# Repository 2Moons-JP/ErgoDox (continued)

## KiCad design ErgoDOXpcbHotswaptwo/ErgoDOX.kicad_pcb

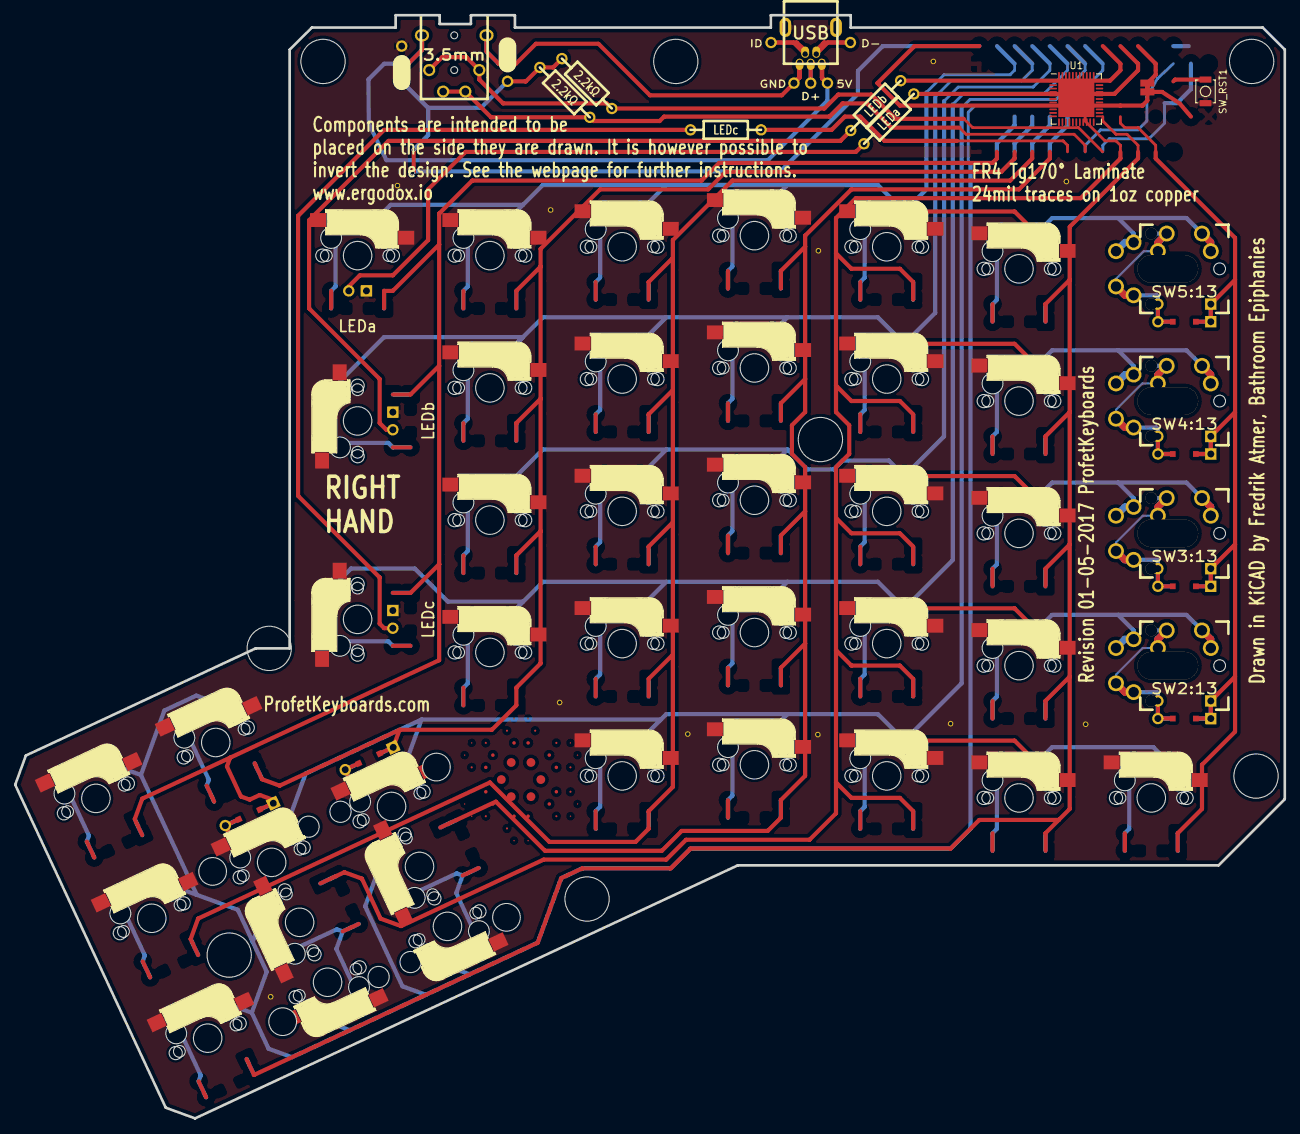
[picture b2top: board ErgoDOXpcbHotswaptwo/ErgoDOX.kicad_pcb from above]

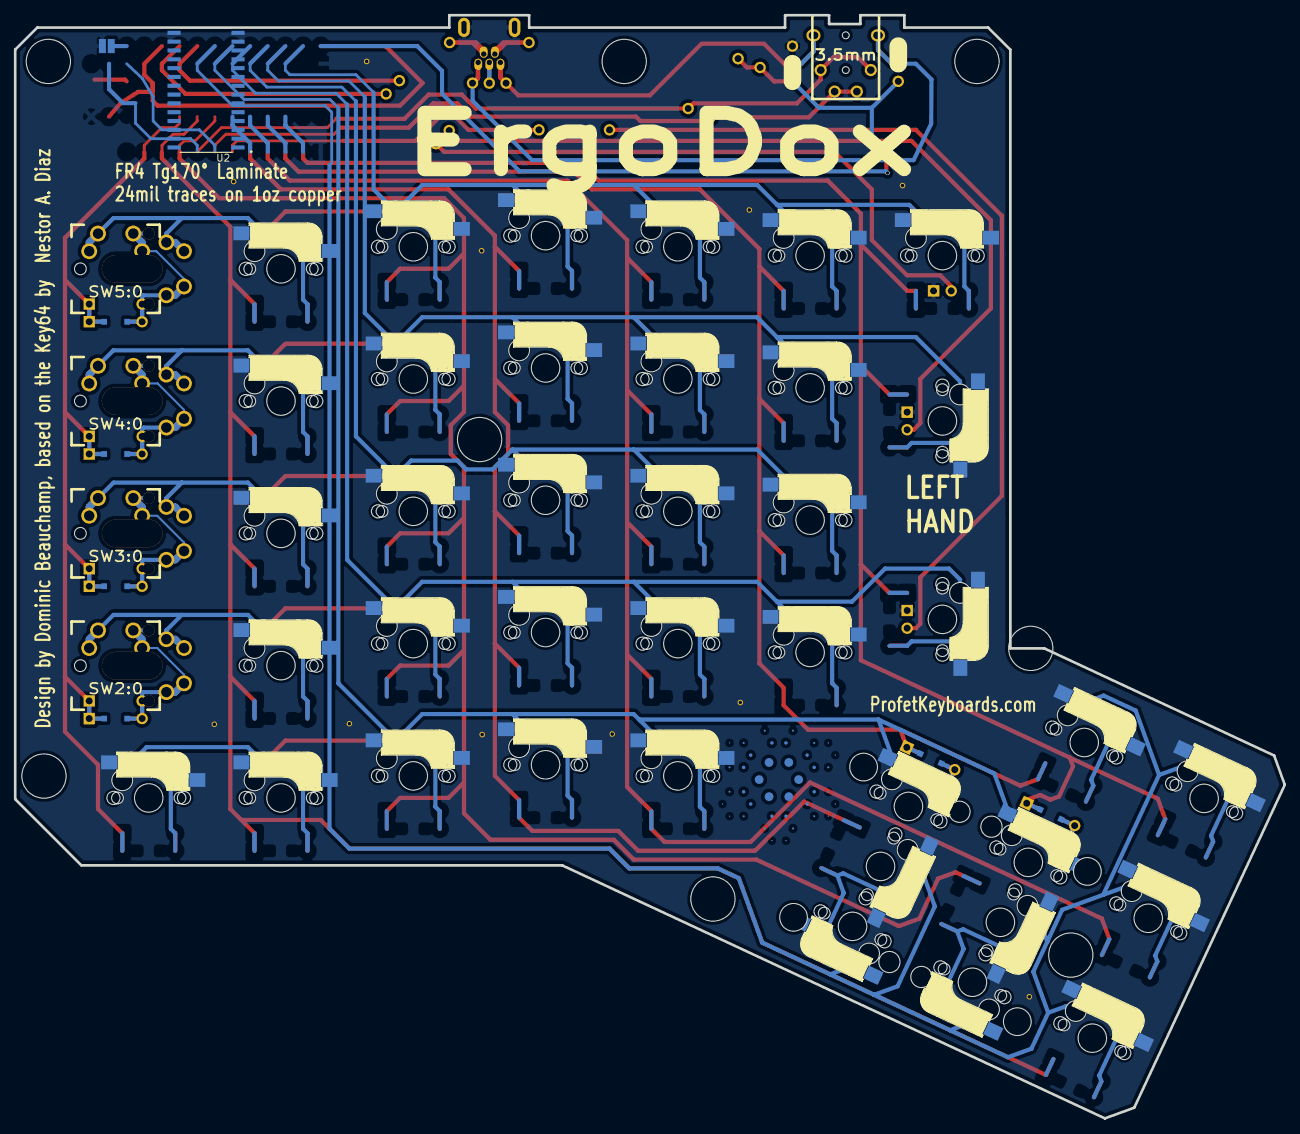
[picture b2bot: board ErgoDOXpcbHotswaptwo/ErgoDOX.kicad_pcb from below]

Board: 2 copper layers, 182.8 x 158.9 mm, 77 parts (4 on the bottom side), 36 nets.

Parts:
D1:7, D1:8: D; DIODE
H99: MECHANICAL; ErgoDOXmech
J1: USB; USBMINImod
J2: 3.5mm; 4pin35mmAudio
J3, J4: JMP; 100PITCH1X3
JP1, JP2: JUMPER; GAP
LED_A1: LEDa; MX_LED
LED_B1: LEDb; MX_LED
LED_C1: LEDc; MX_LED
R1, R2: 2.2kΩ; RESISTOR
RA1: LEDa; RESISTOR
RB1: LEDb; RESISTOR
RC1: LEDc; RESISTOR
S1, S2: STAB200; STAB_PCB940
STAR_1: STAR_FRONT; STAR
STAR_2: STAR_BACK; STAR
STITCHING_VIA: STITCHING_VIA
STITCHING_VIA#2, STITCHING_VIA#3, STITCHING_VIA#4, STITCHING_VIA#5, STITCHING_VIA#6, STITCHING_VIA#7, STITCHING_VIA#8, STITCHING_VIA#9, STITCHING_VIA#10, STITCHING_VIA#11: STITCHING_VIA
SW0:7: SW0:6; CherryMX_MidHeight_Hotswap
SW0:8: SW0:5; CherryMX_MidHeight_Hotswap
SW0:9: SW0:4; CherryMX_MidHeight_Hotswap
SW0:10: SW0:3; CherryMX_MidHeight_Hotswap
SW0:11: SW0:2; CherryMX_MidHeight_Hotswap
SW0:12: SW0:1; CherryMX_MidHeight_Hotswap
SW1:9: SW1:4; CherryMX_MidHeight_Hotswap
SW1:10: SW1:3; CherryMX_MidHeight_Hotswap
SW1:11: SW1:2; CherryMX_MidHeight_Hotswap
SW1:12: SW1:1; CherryMX_MidHeight_Hotswap
SW1:13: SW1:0; CherryMX_MidHeight_Hotswap
SW2:7: SW2:6; CherryMX_MidHeight_Hotswap
SW2:8: SW2:5; CherryMX_MidHeight_Hotswap
SW2:9: SW2:4; CherryMX_MidHeight_Hotswap
SW2:10: SW2:3; CherryMX_MidHeight_Hotswap
SW2:11: SW2:2; CherryMX_MidHeight_Hotswap
SW2:12: SW2:1; CherryMX_MidHeight_Hotswap
SW2:13: SW2:0; MX_FLIP_XX
SW3:8: SW3:5; CherryMX_MidHeight_Hotswap
SW3:9: SW3:4; CherryMX_MidHeight_Hotswap
SW3:10: SW3:3; CherryMX_MidHeight_Hotswap
SW3:11: SW3:2; CherryMX_MidHeight_Hotswap
SW3:12: SW3:1; CherryMX_MidHeight_Hotswap
SW3:13: SW3:0; MX_FLIP_XX
SW4:7: SW4:6; CherryMX_MidHeight_Hotswap
SW4:8: SW4:5; CherryMX_MidHeight_Hotswap
SW4:9: SW4:4; CherryMX_MidHeight_Hotswap
SW4:10: SW4:3; CherryMX_MidHeight_Hotswap
SW4:11: SW4:2; CherryMX_MidHeight_Hotswap
SW4:12: SW4:1; CherryMX_MidHeight_Hotswap
SW4:13: SW4:0; MX_FLIP_XX
SW5:7: SW5:6; CherryMX_MidHeight_Hotswap
SW5:8: SW5:5; CherryMX_MidHeight_Hotswap
SW5:9: SW5:4; CherryMX_MidHeight_Hotswap
SW5:10: SW5:3; CherryMX_MidHeight_Hotswap
SW5:11: SW5:2; CherryMX_MidHeight_Hotswap
SW5:12: SW5:1; CherryMX_MidHeight_Hotswap
SW5:13: SW5:0; MX_FLIP_XX
SW_RST1: SWITCH_PUSH; SW_SPST_B3U-1000P
SX0:10: SX0:3; CherryMX_MidHeight_Hotswap
SX0:11: SX0:2; CherryMX_MidHeight_Hotswap
SX1:7: SX1:6; CherryMX_MidHeight_Hotswap
SX1:8: SX1:5; CherryMX_MidHeight_Hotswap
U1: ATmega32U4-MU; QFN-44-1EP_7x7mm_P0.5mm_EP5.2x5.2mm
U2: MCP23018-E_SO; SOIC127P1030X265-28N

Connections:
/COL0: SW2:13.4, SW3:13.4, SW4:13.4, SW5:13.4, U1.31, U2.20
/COL1: U1.21, U2.21
/COL4: U1.10, U2.24
/COL5: D1:8.2, U1.9, U2.25
/COL6: D1:7.2, U1.8, U2.26
/COL10: U1.11, U2.23
/COL11: U1.20, U2.22
/LED_A: RA1.1, U1.29, U2.10
/LED_B: RB1.1, U1.30, U2.9
/LED_C: RC1.1, U1.12
/ROW0: SW0:7.1, SW0:8.1, SW0:9.1, SW0:10.1, SW0:11.1, SW0:12.1, SX0:10.1, SX0:11.1, U1.36, U2.8
/ROW1: SW1:9.1, SW1:10.1, SW1:11.1, SW1:12.1, SW1:13.1, SX1:7.1, SX1:8.1, U1.37, U2.7
/ROW2: SW2:7.1, SW2:8.1, SW2:9.1, SW2:10.1, SW2:11.1, SW2:12.1, SW2:13.1, U1.38, U2.6
/ROW3: SW3:8.1, SW3:9.1, SW3:10.1, SW3:11.1, SW3:12.1, SW3:13.1, U1.39, U2.5
/ROW4: SW4:7.1, SW4:8.1, SW4:9.1, SW4:10.1, SW4:11.1, SW4:12.1, SW4:13.1, U1.40, U2.4
/ROW5: SW5:7.1, SW5:8.1, SW5:9.1, SW5:10.1, SW5:11.1, SW5:12.1, SW5:13.1, U1.41, U2.3
/SCLM: J2.3, J2.5, R2.2, U1.18, U2.12
/SDAM: J2.2, J2.6, R1.2, U1.19, U2.13
GND: J1.6, J3.3, J4.3, JP2.1, LED_A1.2, LED_B1.2, LED_C1.2, STITCHING_VIA.GND, STITCHING_VIA#2.GND, STITCHING_VIA#3.GND, STITCHING_VIA#4.GND, STITCHING_VIA#5.GND, STITCHING_VIA#6.GND, STITCHING_VIA#7.GND, STITCHING_VIA#8.GND, STITCHING_VIA#9.GND, STITCHING_VIA#10.GND, STITCHING_VIA#11.GND, SW_RST1.2, U2.15
unnamed: D1:7.1, SX1:7.2
unnamed: D1:8.1, SX1:8.2
unnamed: J1.1, J2.4, J4.2
unnamed: J1.5, J2.1, J3.2
unnamed: LED_A1.1, RA1.2
unnamed: LED_B1.1, RB1.2
unnamed: LED_C1.1, RC1.2
unnamed: SW0:10.2, SX0:10.2
unnamed: SW0:11.2, SX0:11.2
unnamed: SW2:13.2, SW2:13.3
unnamed: SW3:13.2, SW3:13.3
unnamed: SW4:13.2, SW4:13.3
unnamed: SW5:13.2, SW5:13.3
unnamed: U1.14, U1.34
unnamed: U1.15, U1.23, U1.35, U1.43, U1.45
unnamed: U1.24, U1.44
VCC: J3.1, J4.1, JP1.1, R1.1, R2.1, U2.16

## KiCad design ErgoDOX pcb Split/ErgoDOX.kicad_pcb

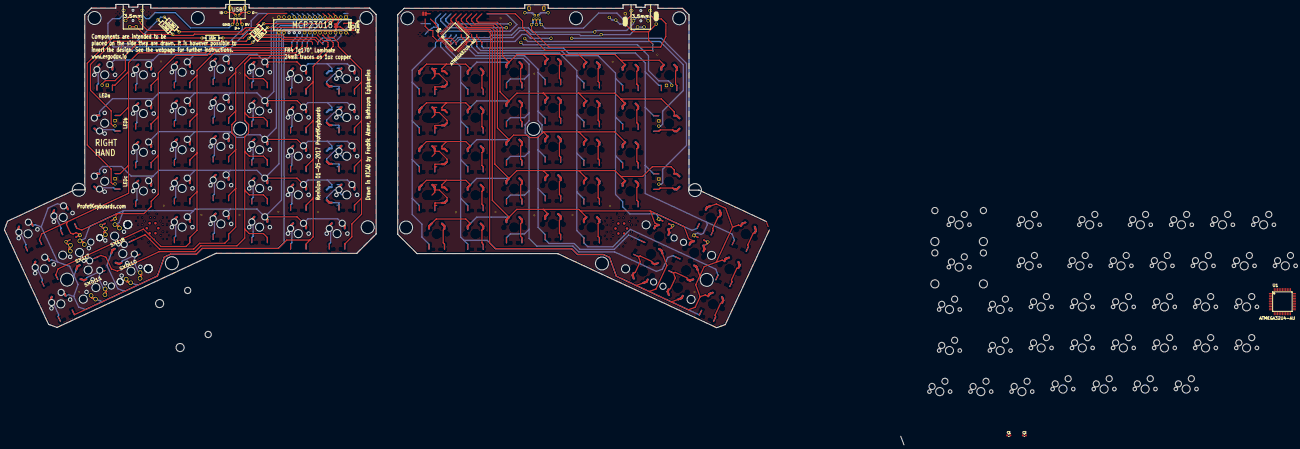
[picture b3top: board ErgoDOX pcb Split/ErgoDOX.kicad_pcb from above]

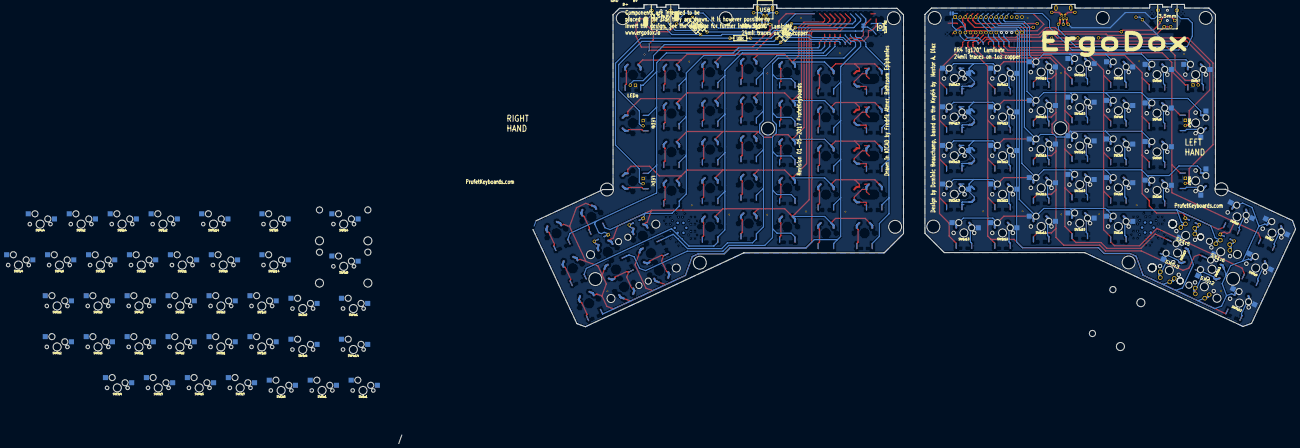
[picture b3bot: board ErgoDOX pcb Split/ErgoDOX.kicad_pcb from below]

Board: 2 copper layers, 149 parts (32 on the bottom side), 43 nets.

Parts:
C1, C2: 1uF; C_0603_1608Metric
D1:7, D1:7#2, D1:8, D1:8#2: D; DIODE
H99, H99#2: MECHANICAL; ErgoDOXmech
J1, J1#2: USB; USBMINImod
J2, J2#2: 3.5mm; 4pin35mmAudio
J3, J4: JMP; 100PITCH1X3
JP1, JP1#2, JP2, JP2#2: JUMPER; GAP
LED_A1, LED_A1#2: LEDa; MX_LED
LED_B1, LED_B1#2: LEDb; MX_LED
LED_C1, LED_C1#2: LEDc; MX_LED
R1, R1#2, R2, R2#2: 2.2kΩ; RESISTOR
RA1, RA1#2: LEDa; RESISTOR
RB1, RB1#2: LEDb; RESISTOR
RC1, RC1#2: LEDc; RESISTOR
S1, S1#2, S2, S2#2: STAB200; STAB_PCB940
STAR_1, STAR_1#2: STAR_FRONT; STAR
STAR_2, STAR_2#2: STAR_BACK; STAR
STITCHING_VIA: STITCHING_VIA
STITCHING_VIA#2, STITCHING_VIA#3, STITCHING_VIA#4, STITCHING_VIA#5, STITCHING_VIA#6, STITCHING_VIA#7, STITCHING_VIA#8, STITCHING_VIA#9, STITCHING_VIA#10, STITCHING_VIA#11, STITCHING_VIA#12, STITCHING_VIA#13, STITCHING_VIA#14, STITCHING_VIA#15, STITCHING_VIA#16, STITCHING_VIA#17, STITCHING_VIA#18, STITCHING_VIA#19, STITCHING_VIA#20, STITCHING_VIA#21, STITCHING_VIA#22: STITCHING_VIA
SW0:1, SW0:7: SW0:6; MXOnly-1U-Hotswap
SW0:2, SW0:8: SW0:5; MXOnly-1U-Hotswap
SW0:3, SW0:9: SW0:4; MXOnly-1U-Hotswap
SW0:4: SW0:3; MXOnly-2U-Hotswap
SW0:5, SW0:11: SW0:2; MXOnly-2U-Hotswap
SW0:6, SW0:12: SW0:1; MXOnly-1U-Hotswap
SW0:10: SW0:3; MXOnly-2U-Hotswap-ReversedStabilizers
SW1:1, SW1:9: SW1:4; MXOnly-1U-Hotswap
SW1:2, SW1:10: SW1:3; MXOnly-1U-Hotswap
SW1:3, SW1:11: SW1:2; MXOnly-1U-Hotswap
SW1:4, SW1:12: SW1:1; MXOnly-1U-Hotswap
SW1:5, SW1:13: SW1:0; MXOnly-1U-Hotswap
SW2:1, SW2:7: SW2:6; MXOnly-1U-Hotswap
SW2:2, SW2:8: SW2:5; MXOnly-1U-Hotswap
SW2:3, SW2:9: SW2:4; MXOnly-1U-Hotswap
SW2:4, SW2:10: SW2:3; MXOnly-1U-Hotswap
SW2:5, SW2:11: SW2:2; MXOnly-1U-Hotswap
SW2:6, SW2:12: SW2:1; MXOnly-1U-Hotswap
SW2:13, SW2:14: SW2:0; MXOnly-1.5U-Hotswap
SW3:1, SW3:8: SW3:5; MXOnly-1U-Hotswap
SW3:2, SW3:9: SW3:4; MXOnly-1U-Hotswap
SW3:3, SW3:10: SW3:3; MXOnly-1U-Hotswap
SW3:4, SW3:11: SW3:2; MXOnly-1U-Hotswap
SW3:5, SW3:12: SW3:1; MXOnly-1U-Hotswap
SW3:6, SW3:13: SW3:0; MXOnly-1.5U-Hotswap
SW4:1, SW4:7: SW4:6; MXOnly-1.5U-Hotswap
SW4:2, SW4:8: SW4:5; MXOnly-1U-Hotswap
SW4:3, SW4:9: SW4:4; MXOnly-1U-Hotswap
SW4:4, SW4:10: SW4:3; MXOnly-1U-Hotswap
SW4:5, SW4:11: SW4:2; MXOnly-1U-Hotswap
SW4:6, SW4:12: SW4:1; MXOnly-1U-Hotswap
SW4:13, SW4:14: SW4:0; MXOnly-1.5U-Hotswap
SW5:1, SW5:7: SW5:6; MXOnly-1U-Hotswap
SW5:2, SW5:8: SW5:5; MXOnly-1U-Hotswap
SW5:3, SW5:9: SW5:4; MXOnly-1U-Hotswap
SW5:4, SW5:10: SW5:3; MXOnly-1U-Hotswap
SW5:5, SW5:11: SW5:2; MXOnly-1U-Hotswap
SW5:6, SW5:12: SW5:1; MXOnly-1U-Hotswap
SW5:13, SW5:14: SW5:0; MXOnly-1.5U-Hotswap
SW_RST1, SW_RST1#2: SWITCH_PUSH; SW_SPST_B3U-1000P
SX0:10: SX0:3; MX_FLIP
SX0:11: SX0:2; MX_FLIP
SX1:7: SX1:6; MX_FLIP
SX1:8: SX1:5; MX_FLIP
U1, U4: ATMEGA32U4-AU
U2: MCP23018; DIP28_300

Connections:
/COL0: U2.20, U4.31
/COL1: U2.21, U4.21
/COL4: U2.24, U4.10
/COL5: D1:8.2, D1:8#2.2, U2.25, U4.9
/COL6: D1:7.2, D1:7#2.2, U2.26, U4.8
/COL10: U2.23, U4.11
/COL11: U2.22, U4.20
/LED_A: RA1.1, RA1#2.1, U2.10, U4.29
/LED_B: RB1.1, RB1#2.1, U2.9, U4.30
/LED_C: RC1.1, RC1#2.1, U4.12
/ROW0: SW0:7.1, SW0:8.1, SW0:9.1, SW0:10.1, SW0:11.1, SW0:12.1, SX0:10.1, SX0:11.1, U2.8, U4.36
/ROW1: SW1:9.1, SW1:10.1, SW1:11.1, SW1:12.1, SW1:13.1, SX1:7.1, SX1:8.1, U2.7, U4.37
/ROW2: SW2:7.1, SW2:8.1, SW2:9.1, SW2:10.1, SW2:11.1, SW2:12.1, SW2:13.1, U2.6, U4.38
/ROW3: SW3:8.1, SW3:9.1, SW3:10.1, SW3:11.1, SW3:12.1, SW3:13.1, U2.5, U4.39
/ROW4: SW4:7.1, SW4:8.1, SW4:9.1, SW4:10.1, SW4:11.1, SW4:12.1, SW4:13.1, U2.4, U4.40
/ROW5: SW5:7.1, SW5:8.1, SW5:9.1, SW5:10.1, SW5:11.1, SW5:12.1, SW5:13.1, U2.3, U4.41
/RST: SW_RST1.1, SW_RST1#2.1
/Right Hand/ROW0: SW0:1.1, SW0:2.1, SW0:3.1, SW0:4.1, SW0:5.1, SW0:6.1, U1.36
/Right Hand/ROW1: SW1:1.1, SW1:2.1, SW1:3.1, SW1:4.1, SW1:5.1, U1.37
/Right Hand/ROW2: SW2:1.1, SW2:2.1, SW2:3.1, SW2:4.1, SW2:5.1, SW2:6.1, SW2:14.1, U1.38
/Right Hand/ROW3: SW3:1.1, SW3:2.1, SW3:3.1, SW3:4.1, SW3:5.1, SW3:6.1, U1.39
/Right Hand/ROW4: SW4:1.1, SW4:2.1, SW4:3.1, SW4:4.1, SW4:5.1, SW4:6.1, SW4:14.1, U1.40
/Right Hand/ROW5: SW5:1.1, SW5:2.1, SW5:3.1, SW5:4.1, SW5:5.1, SW5:6.1, SW5:14.1, U1.41
/SCLM: J2.3, J2.5, J2#2.3, J2#2.5, R2.2, R2#2.2, U2.12
/SDAM: J2.2, J2.6, J2#2.2, J2#2.6, R1.2, R1#2.2, U2.13
GND: C1.2, C2.2, J1.6, J1#2.6, J3.3, J4.3, JP2.1, JP2#2.1, LED_A1.2, LED_A1#2.2, LED_B1.2, LED_B1#2.2, LED_C1.2, LED_C1#2.2, STITCHING_VIA.GND, STITCHING_VIA#2.GND, STITCHING_VIA#3.GND, STITCHING_VIA#4.GND, STITCHING_VIA#5.GND, STITCHING_VIA#6.GND, STITCHING_VIA#7.GND, STITCHING_VIA#8.GND, STITCHING_VIA#9.GND, STITCHING_VIA#10.GND, STITCHING_VIA#11.GND, STITCHING_VIA#12.GND, STITCHING_VIA#13.GND, STITCHING_VIA#14.GND, STITCHING_VIA#15.GND, STITCHING_VIA#16.GND, STITCHING_VIA#17.GND, STITCHING_VIA#18.GND, STITCHING_VIA#19.GND, STITCHING_VIA#20.GND, STITCHING_VIA#21.GND, STITCHING_VIA#22.GND, SW_RST1.2, SW_RST1#2.2, U1.5, U1.15, U1.23, U1.35, U1.43, U2.1, U2.15, U4.5, U4.15, U4.23, U4.35, U4.43
unnamed: C1.1, U4.6
unnamed: C2.1, U1.6
unnamed: D1:7.1, D1:7#2.1, SX1:7.2
unnamed: D1:8.1, D1:8#2.1, SX1:8.2
unnamed: J1.1, J1#2.1, J2.4, J2#2.4, J4.2
unnamed: J1.2, J1#2.2
unnamed: J1.3, J1#2.3
unnamed: J1.4, J1#2.4
unnamed: J1.5, J1#2.5, J2.1, J2#2.1, J3.2
unnamed: LED_A1.1, LED_A1#2.1, RA1.2, RA1#2.2
unnamed: LED_B1.1, LED_B1#2.1, RB1.2, RB1#2.2
unnamed: LED_C1.1, LED_C1#2.1, RC1.2, RC1#2.2
unnamed: SW0:10.2, SX0:10.2
unnamed: SW0:11.2, SX0:11.2
SCLS: U1.18, U4.18
SDAS: U1.19, U4.19
VCC: J3.1, J4.1, JP1.1, JP1#2.1, R1.1, R1#2.1, R2.1, R2#2.1, U1.2, U1.7, U1.14, U1.24, U1.34, U1.44, U2.11, U2.16, U4.2, U4.7, U4.14, U4.24, U4.34, U4.44

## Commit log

2021-01-24 New ErgoDOX PCB
2021-01-27 1/27/2021
2021-01-27 1/28/2021
2021-01-27 New PCB
2021-02-01 2/1/2021
2021-02-07 2/8/2021
2021-02-09 Add new 23018
2021-02-09 2/9/2021
2021-02-11 2/11/2021
2021-02-20 2/20/2021
2021-03-12 New Hotswap
